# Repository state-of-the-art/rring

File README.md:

# RRing

Smart-Ring opensource project

## Features

* BLE connection to smartphone
* Programmable button
* Integrated IMU for positioning in space (3d mouse)
* Show clock on little led display
* Silent vibro alarm, notifications and feedback
* Wireless charging

## BOM

* SOC:
   * MCU: DA14531-OG2 (WLCSP 17)
   * BT Antenna: ANT3216LL00R2400A (SMD Chip)
* Power:
   * Wireless charger: LTC4124 (LQFN 12)
   * Wireless charger antenna: ???
   * LDO: ADP160ACBZ-1.8-R7 (WLCSP 4)
   * Battery: ??? TODO ??? Curved, Li, ~7x33x17.7mm
* Clock display:
   * 4 digit 7 segment LED driver: TCA6418EYFPR (DSBGA 25)
   * 30 LEDs: IN-S21AT (0201)
* Control:
   * Button: KMT071NGJLHS (IP68)
   * IMU: ICM-20948 (QFN 24)
* Additional:
   * Vibro feedback: [EM custom](models/vibro_device-mk1.blend)

## Development

For PoC I used DA14531-00FXDEVKT-U (UM-B-125) - which is a small usb devboard with embedded debug
chip (uart/jtag), have spi flash to not disturb OTP ROM and safely play with firmware, just enough
to start. For sure you will need SDK for DA14531, you can easily get it on the manufacturer site.

Must read docs:
* [About devboard](https://www.renesas.com/us/en/document/mat/um-b-125-user-manual-da14531-usb-development-kit-hardware)
* [SDK6 tutorial](https://lpccs-docs.renesas.com/Tutorial_SDK6/introduction.html)
* [SDK6 peripherals tutorial](https://lpccs-docs.renesas.com/da145xx_tutorial_sdk6_peripherals/introduction.html)
* [SDK6 debugging](https://lpccs-docs.renesas.com/tutorial_da145xx_debugging_techniques/index.html)

### How to Build & Run

1. Download SDK (6.0.18.1182.1) and unpack to any directory
2. Download SmartSnippets Studio (2.0.20.4060), eclipse based IDE, and install it to the env
3. Run SmartSnippets Studio and specify the SDK - it will be used as workspace
4. Move to Exclipse IDE from welcome screen (ensure all the deps are installed)
5. Import the project as `General -> Projects from Folder or Archive` and navigate repo directory
`src/firmware/Eclipse`
6. Select DA14531 build profile and build the imported `rring` project
7. Connect USB devboard and run `Debug RAM_DA14531` to run the firmware on the chip

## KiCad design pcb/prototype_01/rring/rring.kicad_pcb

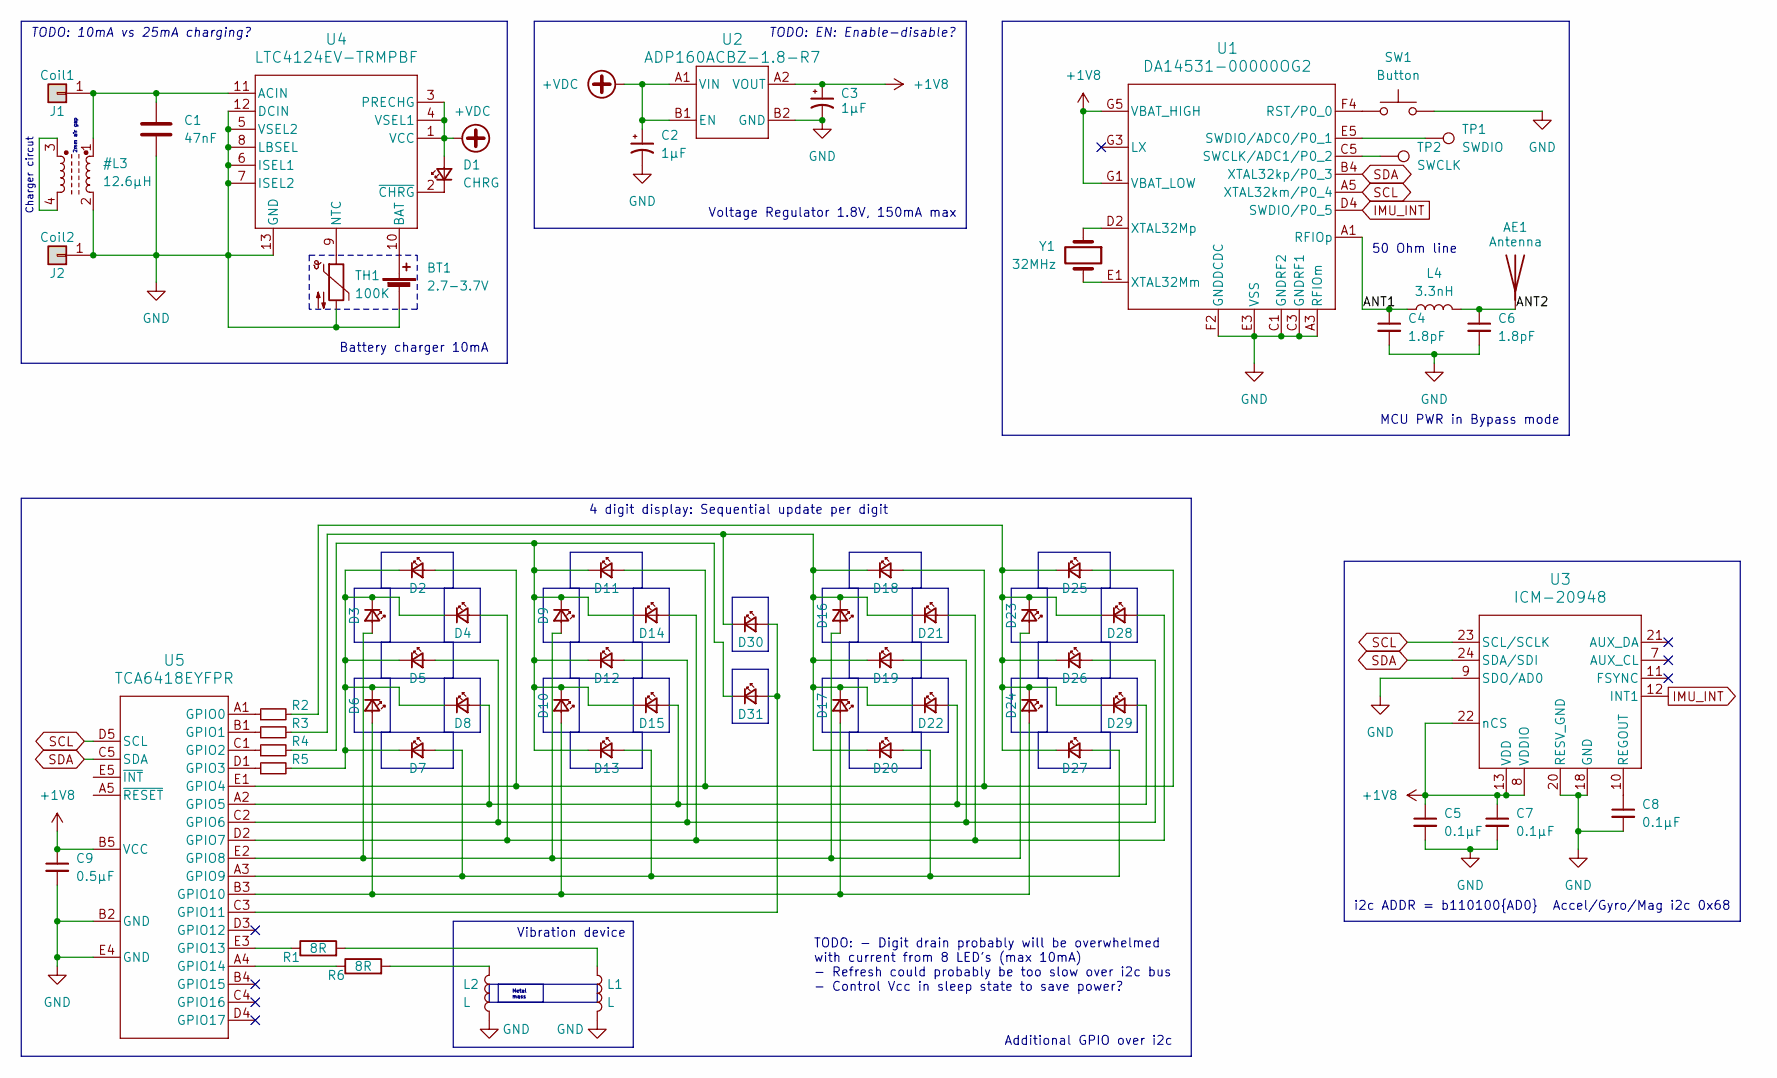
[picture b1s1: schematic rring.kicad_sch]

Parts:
AE1: Antenna; ANT_ANT3216_YAG
BT1: 2.7-3.7V; R_0805_2012Metric
C1: 47nF; C_0201_0603Metric
C2, C3: 1µF; C_0201_0603Metric
C4, C6: 1.8pF; C_0201_0603Metric
C5, C7, C8: 0.1µF; C_0201_0603Metric
C9: 0.5µF; C_0201_0603Metric
D1: CHRG; D_0201_0603Metric
D2, D3, D4, D5, D6, D7, D8, D9, D10, D11, D12, D13, D14, D15, D16, D17, D18, D19, D20, D21, D22, D23, D24, D25, D26, D27, D28, D29, D30, D31: DIG; D_0201_0603Metric
J1: Coil1; Conn_Pad_0.5x0.5mm
J2: Coil2; Conn_Pad_0.5x0.5mm
L1, L2: L; L_0805_2012Metric
L4: 3.3nH; L_0201_0603Metric
R1, R6: 8R; R_0201_0603Metric
R2, R3, R4, R5: R_Small; R_0201_0603Metric
SW1: Button; KMT0_push_3x2.6
TH1: 100K; R_0402_1005Metric
TP1: SWDIO; TestPoint_Pad_D0.5mm
TP2: SWCLK; TestPoint_Pad_D0.5mm
U1: DA14531-00000OG2; DA14531-00000OG2_DIL
U2: ADP160ACBZ-1.8-R7; CB_4_1_ADI
U3: ICM-20948; QFN24_3X3X0P9_IVS
U4: LTC4124EV-TRMPBF; LQFN12_ADI
U5: TCA6418EYFPR; YFP25_TEX
Y1: 32MHz; Crystal_SMD_2016-4Pin_2.0x1.6mm

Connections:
+1V8: C3.1, C5.1, C7.1, C9.1, U1.G1 (VBAT_LOW), U1.G5 (VBAT_HIGH), U2.A2 (VOUT), U3.8 (VDDIO), U3.13 (VDD), U3.22 (nCS), U5.B5 (VCC)
+VDC: C2.1, D1.2 (A), U2.A1 (VIN), U2.B1 (EN), U4.1 (VCC), U4.3 (PRECHG), U4.4 (VSEL1)
/ANT1: C4.1, L4.1, U1.A1 (RFIOp)
/ANT2: AE1.1 (A), C6.1, L4.2
IMU_INT: U1.D4 (SWDIO/P0_5), U3.12 (INT1)
unnamed: BT1.1 (+), U4.10 (BAT)
unnamed: D1.1 (K), U4.2 (~CHRG)
unnamed: D2.1 (K), D3.1 (K), D4.1 (K), D5.1 (K), D6.1 (K), D7.1 (K), D8.1 (K), R5.2
unnamed: D6.2 (A), D10.2 (A), D17.2 (A), D24.2 (A), U5.B3 (GPIO10)
unnamed: D9.1 (K), D10.1 (K), D11.1 (K), D12.1 (K), D13.1 (K), D14.1 (K), D15.1 (K), D31.1 (K), R4.2
unnamed: D2.2 (A), D11.2 (A), D18.2 (A), D25.2 (A), U5.E1 (GPIO4)
unnamed: D5.2 (A), D12.2 (A), D19.2 (A), D26.2 (A), U5.C2 (GPIO6)
unnamed: D7.2 (A), D13.2 (A), D20.2 (A), D27.2 (A), U5.A3 (GPIO9)
unnamed: D4.2 (A), D14.2 (A), D21.2 (A), D28.2 (A), U5.D2 (GPIO7)
unnamed: D8.2 (A), D15.2 (A), D22.2 (A), D29.2 (A), U5.A2 (GPIO5)
unnamed: D3.2 (A), D9.2 (A), D16.2 (A), D23.2 (A), U5.E2 (GPIO8)
unnamed: D16.1 (K), D17.1 (K), D18.1 (K), D19.1 (K), D20.1 (K), D21.1 (K), D22.1 (K), D30.1 (K), R3.2
unnamed: D23.1 (K), D24.1 (K), D25.1 (K), D26.1 (K), D27.1 (K), D28.1 (K), D29.1 (K), R2.2
unnamed: D30.2 (A), D31.2 (A), U5.C3 (GPIO11)
unnamed: L1.1, R1.2
unnamed: L2.2, R6.2
unnamed: SW1.1, U1.F4 (RST/P0_0)
unnamed: TP2.1, U1.C5 (SWCLK/ADC1/P0_2)
unnamed: TP1.1, U1.E5 (SWDIO/ADC0/P0_1)
unnamed: U1.E1 (XTAL32Mm), Y1.2
unnamed: U1.D2 (XTAL32Mp), Y1.1
unnamed: C8.1, U3.10 (REGOUT)
unnamed: TH1.1, U4.9 (NTC)
unnamed: R2.1, U5.A1 (GPIO0)
unnamed: R3.1, U5.B1 (GPIO1)
unnamed: R4.1, U5.C1 (GPIO2)
unnamed: R5.1, U5.D1 (GPIO3)
unnamed: R1.1, U5.E3 (GPIO13)
unnamed: R6.1, U5.A4 (GPIO14)
SCL: U1.A5 (XTAL32km/P0_4), U3.23 (SCL/SCLK), U5.D5 (SCL)
SDA: U1.B4 (XTAL32kp/P0_3), U3.24 (SDA/SDI), U5.C5 (SDA)

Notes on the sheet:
Additional GPIO over i2c
Metal mass
TODO: EN: Enable-disable?
i2c ADDR = b110100{AD0}
Voltage Regulator 1.8V, 150mA max
4 digit display: Sequential update per digit
50 Ohm line
Charger circut
TODO: - Digit drain probably will be overwhelmed with current from 8 LED's (max 10mA) - Refresh could probably be too slow over i2c bus - Control Vcc in sleep state to save power?
2mm air gap
Vibration device
TODO: 10mA vs 25mA charging?
Accel/Gyro/Mag i2c 0x68
MCU PWR in Bypass mode
Battery charger 10mA

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
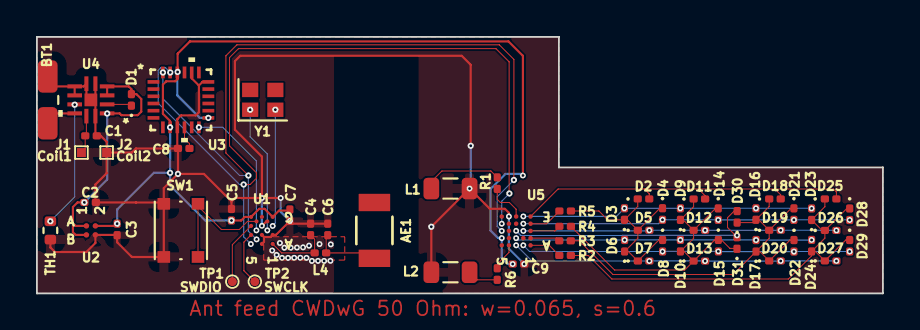
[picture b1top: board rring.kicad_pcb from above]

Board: 2 copper layers, 47.0 x 14.2 mm, 63 parts (0 on the bottom side), 38 nets.

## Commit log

2023-06-09 Added readme and model images
2023-06-09 Added ring model
2023-06-09 Added datasheets of the used components
2023-06-24 Added hw recommendations doc for mcu
2023-06-24 Added docs for the mcu development
2023-06-26 Added the basic firmware based on SDK6 and Eclipse
2023-07-31 Added first and not working well vibro device & smd antenna
2023-07-31 Added schematics and initial PCB
2023-08-30 Completed the main PCB of the first prototype
